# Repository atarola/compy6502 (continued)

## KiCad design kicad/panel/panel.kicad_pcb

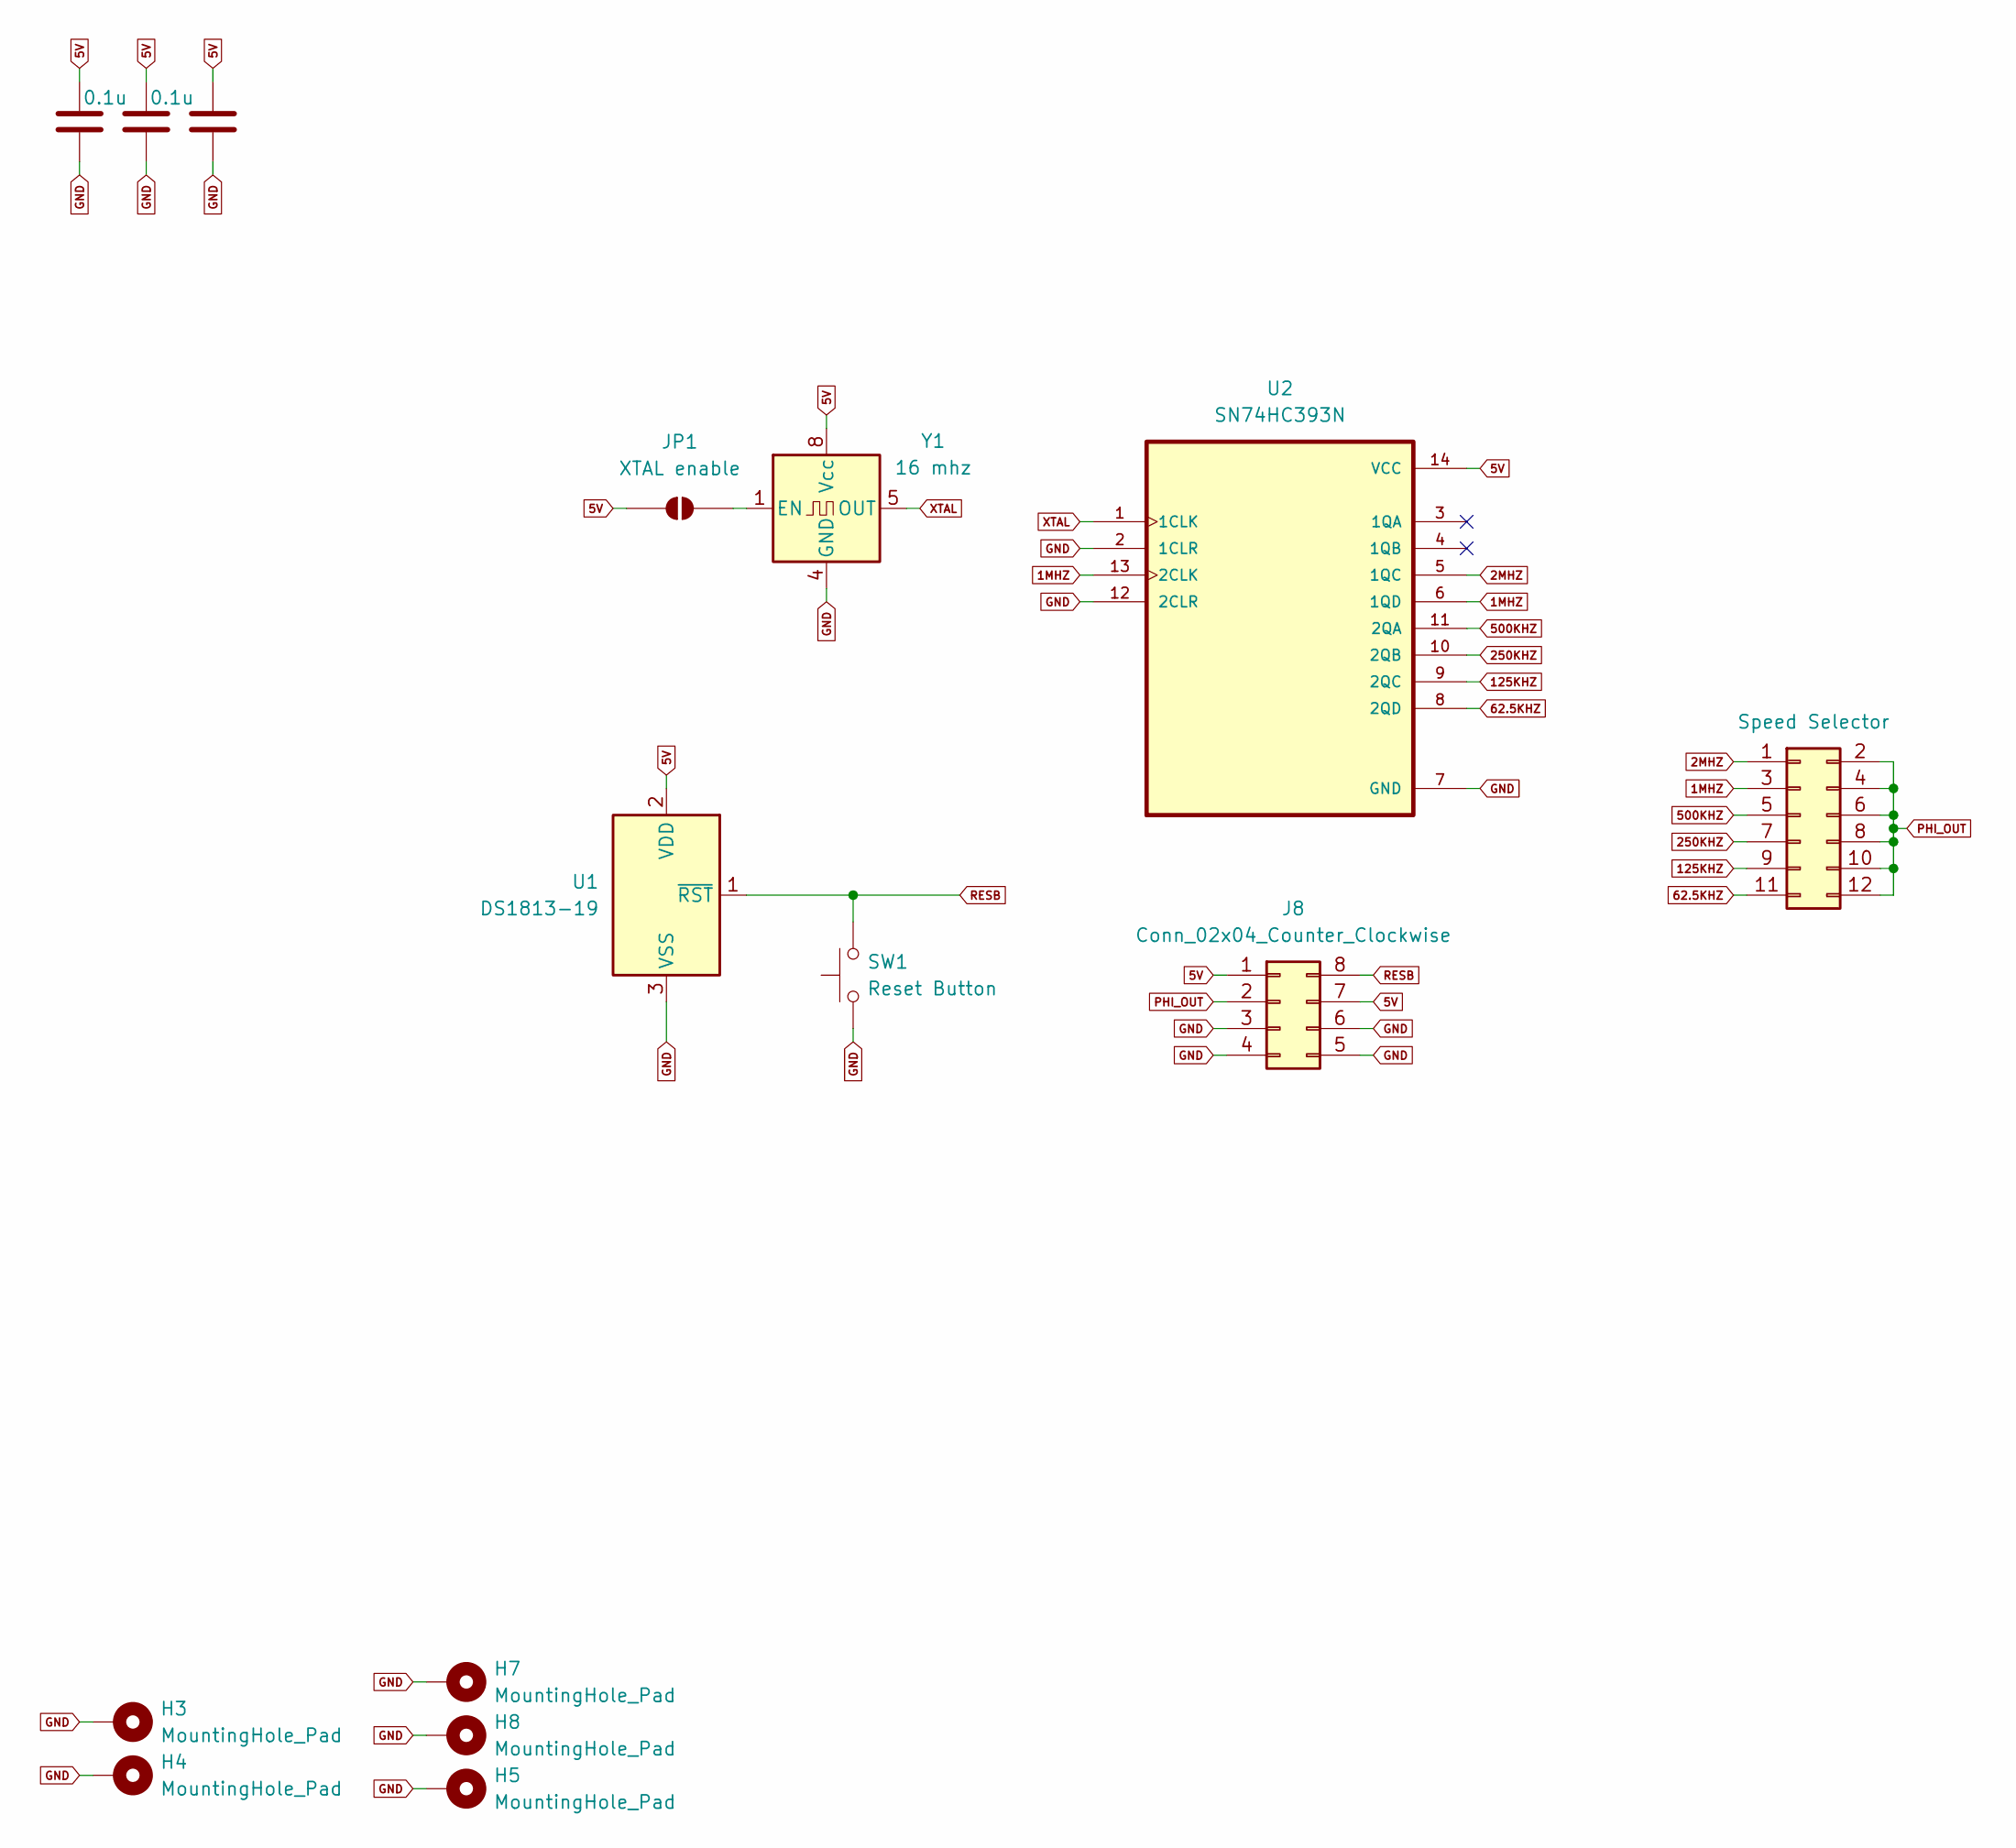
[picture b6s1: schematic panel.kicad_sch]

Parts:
C6, C7, C8: 0.1u; C_Disc_D3.8mm_W2.6mm_P2.50mm
H3, H4, H5, H7, H8: MountingHole_Pad; MountingHole_2.2mm_M2_Pad
J2: Speed Selector; PinHeader_2x06_P2.54mm_Vertical
J8: Conn_02x04_Counter_Clockwise; PinHeader_2x04_P2.54mm_Vertical
JP1: XTAL enable; SolderJumper-2_P1.3mm_Open_TrianglePad1.0x1.5mm
SW1: Reset Button; SW_SPST_Omron_B3F-40xx
U1: DS1813-19; TO-92_Inline
U2: SN74HC393N; DIP-14_W7.62mm_Socket_LongPads
Y1: 16 mhz; Oscillator_DIP-8

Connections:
1MHZ: J2.3, U2.6 (1QD), U2.13 (2CLK)
2MHZ: J2.1, U2.5 (1QC)
5V: C6.1, C7.1, C8.1, J8.1, J8.7, JP1.1 (A), U1.2 (VDD), U2.14 (VCC), Y1.8 (Vcc)
62.5KHZ: J2.11, U2.8 (2QD)
125KHZ: J2.9, U2.9 (2QC)
250KHZ: J2.7, U2.10 (2QB)
500KHZ: J2.5, U2.11 (2QA)
GND: C6.2, C7.2, C8.2, H3.1 (1_1), H4.1 (1_1), H5.1 (1_1), H7.1 (1_1), H8.1 (1_1), J8.3, J8.4, J8.5, J8.6, SW1.1, U1.3 (VSS), U2.2 (1CLR), U2.7 (GND), U2.12 (2CLR), Y1.4 (GND)
unnamed: JP1.2 (B), Y1.1 (EN)
PHI_OUT: J2.2, J2.4, J2.6, J2.8, J2.10, J2.12, J8.2
RESB: J8.8, SW1.2, U1.1 (~RST)
XTAL: U2.1 (1CLK), Y1.5 (OUT)

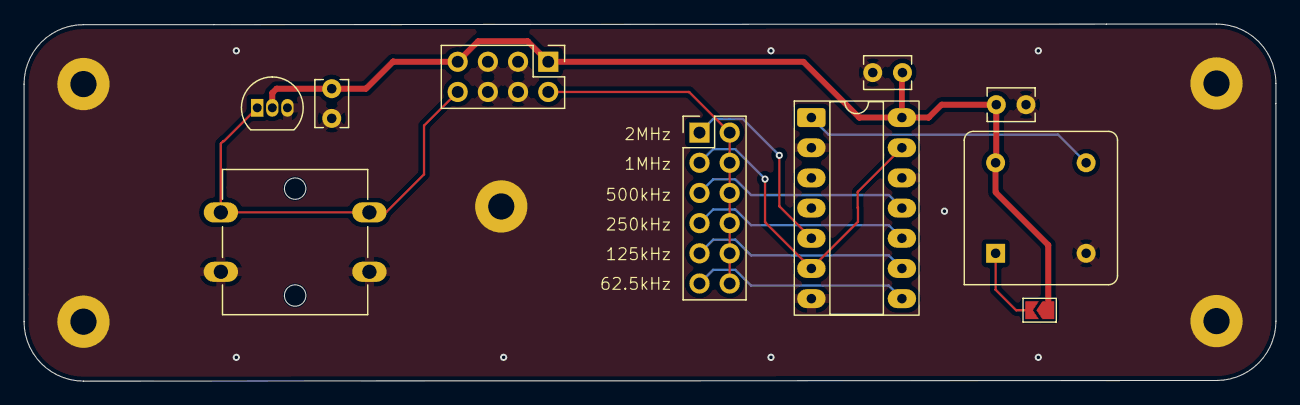
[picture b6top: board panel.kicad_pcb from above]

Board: 2 copper layers, 105.4 x 30.0 mm, 15 parts (0 on the bottom side), 12 nets.

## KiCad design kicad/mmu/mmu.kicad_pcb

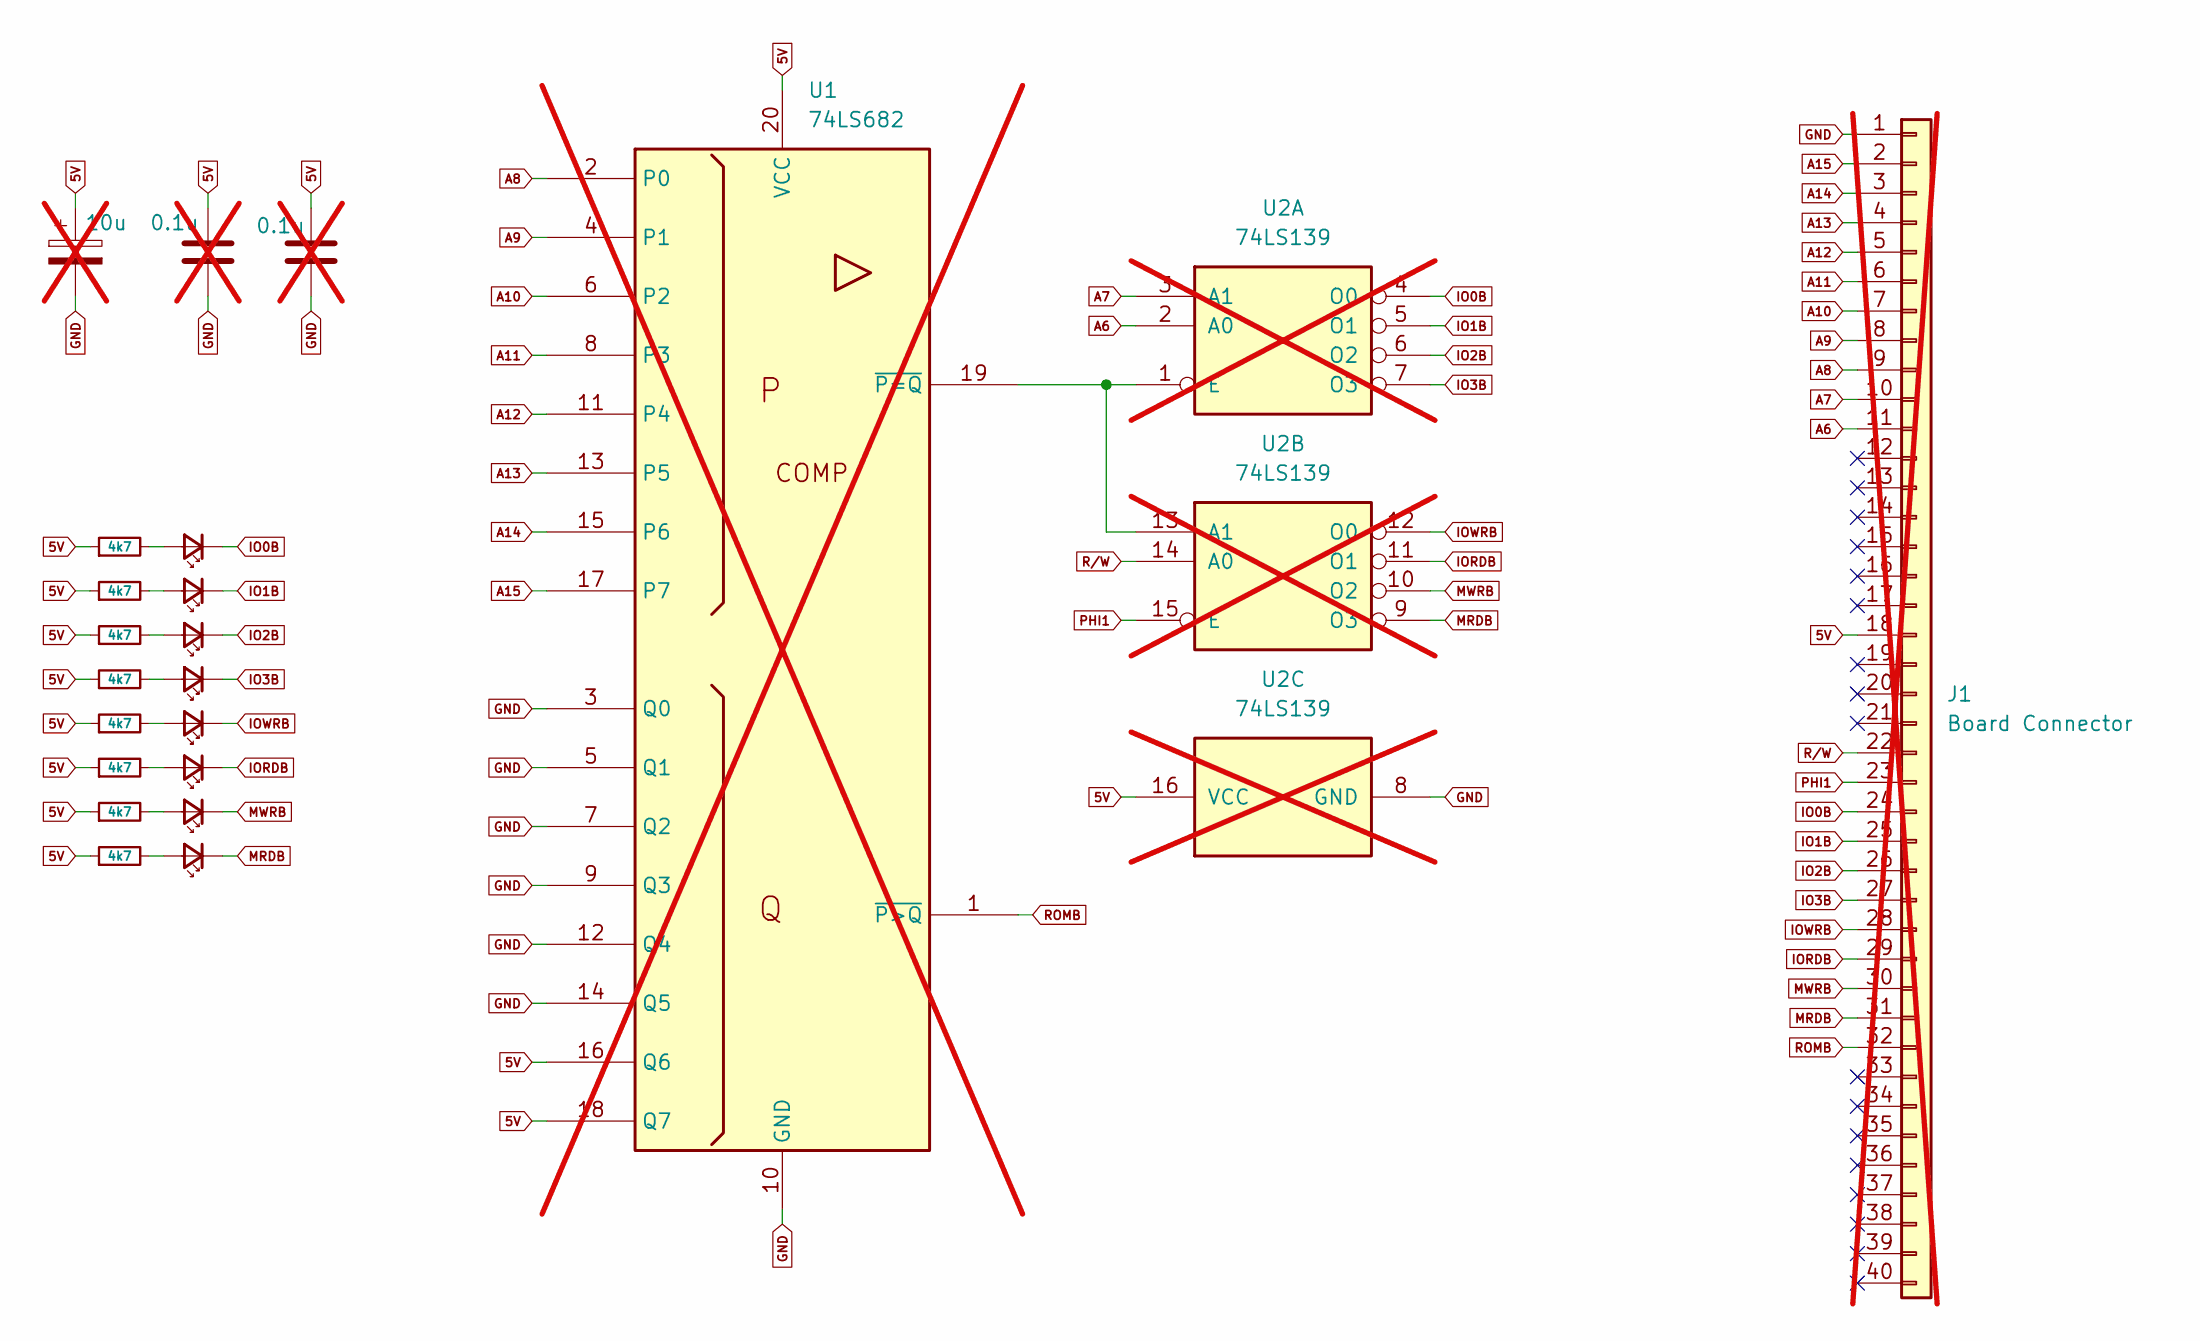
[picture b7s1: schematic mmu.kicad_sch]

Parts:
C1, C2: 0.1u; C_Disc_D3.0mm_W1.6mm_P2.50mm; not fitted
C3: 10u; CP_Radial_D5.0mm_P2.50mm; not fitted
D1, D2, D3, D4, D5, D6, D7, D8: LED_Small; LED_0603_1608Metric
J1: Board Connector; PinHeader_1x40_P2.54mm_Horizontal; not fitted
R1, R2, R3, R4, R5, R6, R7, R8: 4k7; R_0603_1608Metric
U1: 74LS682; DIP-20_W7.62mm_Socket; not fitted
U2: 74LS139; DIP-16_W7.62mm_Socket; not fitted

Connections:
5V: C1.1, C2.1, C3.1, J1.18, R1.1, R2.1, R3.1, R4.1, R5.1, R6.1, R7.1, R8.1, U1.16 (Q6), U1.18 (Q7), U1.20 (VCC), U2.16 (VCC)
A6: J1.11, U2.2 (A0)
A7: J1.10, U2.3 (A1)
A8: J1.9, U1.2 (P0)
A9: J1.8, U1.4 (P1)
A10: J1.7, U1.6 (P2)
A11: J1.6, U1.8 (P3)
A12: J1.5, U1.11 (P4)
A13: J1.4, U1.13 (P5)
A14: J1.3, U1.15 (P6)
A15: J1.2, U1.17 (P7)
GND: C1.2, C2.2, C3.2, J1.1, U1.3 (Q0), U1.5 (Q1), U1.7 (Q2), U1.9 (Q3), U1.10 (GND), U1.12 (Q4), U1.14 (Q5), U2.8 (GND)
IO0B: D1.1 (K), J1.24, U2.4 (O0)
IO1B: D2.1 (K), J1.25, U2.5 (O1)
IO2B: D3.1 (K), J1.26, U2.6 (O2)
IO3B: D4.1 (K), J1.27, U2.7 (O3)
IORDB: D6.1 (K), J1.29, U2.11 (O1)
IOWRB: D5.1 (K), J1.28, U2.12 (O0)
MRDB: D8.1 (K), J1.31, U2.9 (O3)
MWRB: D7.1 (K), J1.30, U2.10 (O2)
unnamed: D1.2 (A), R1.2
unnamed: D2.2 (A), R2.2
unnamed: D3.2 (A), R3.2
unnamed: D4.2 (A), R4.2
unnamed: D5.2 (A), R5.2
unnamed: D6.2 (A), R6.2
unnamed: D7.2 (A), R7.2
unnamed: D8.2 (A), R8.2
unnamed: U1.19 (~P=Q), U2.1 (E), U2.13 (A1)
PHI1: J1.23, U2.15 (E)
ROMB: J1.32, U1.1 (~P>Q)
R/W: J1.22, U2.14 (A0)

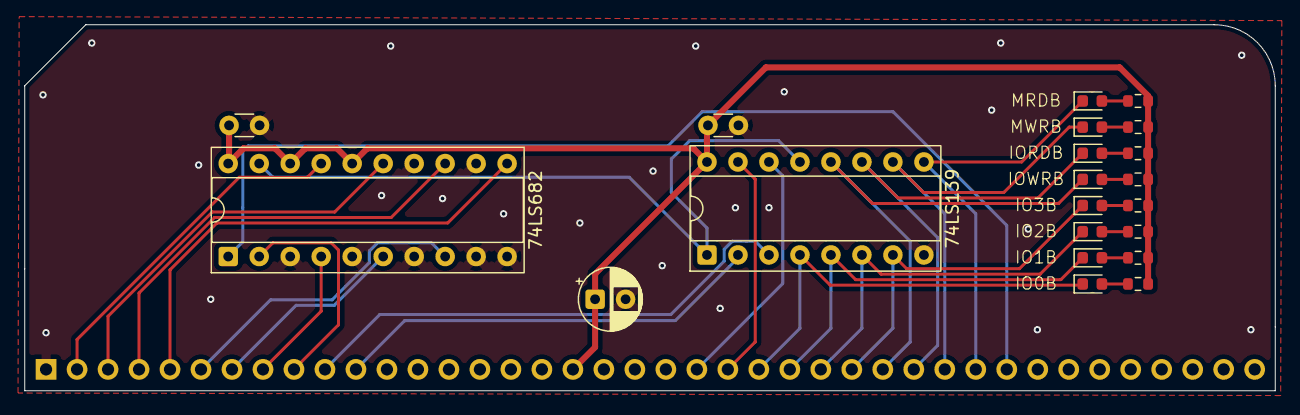
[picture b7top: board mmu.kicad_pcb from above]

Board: 2 copper layers, 102.5 x 30.0 mm, 22 parts (1 on the bottom side), 32 nets.

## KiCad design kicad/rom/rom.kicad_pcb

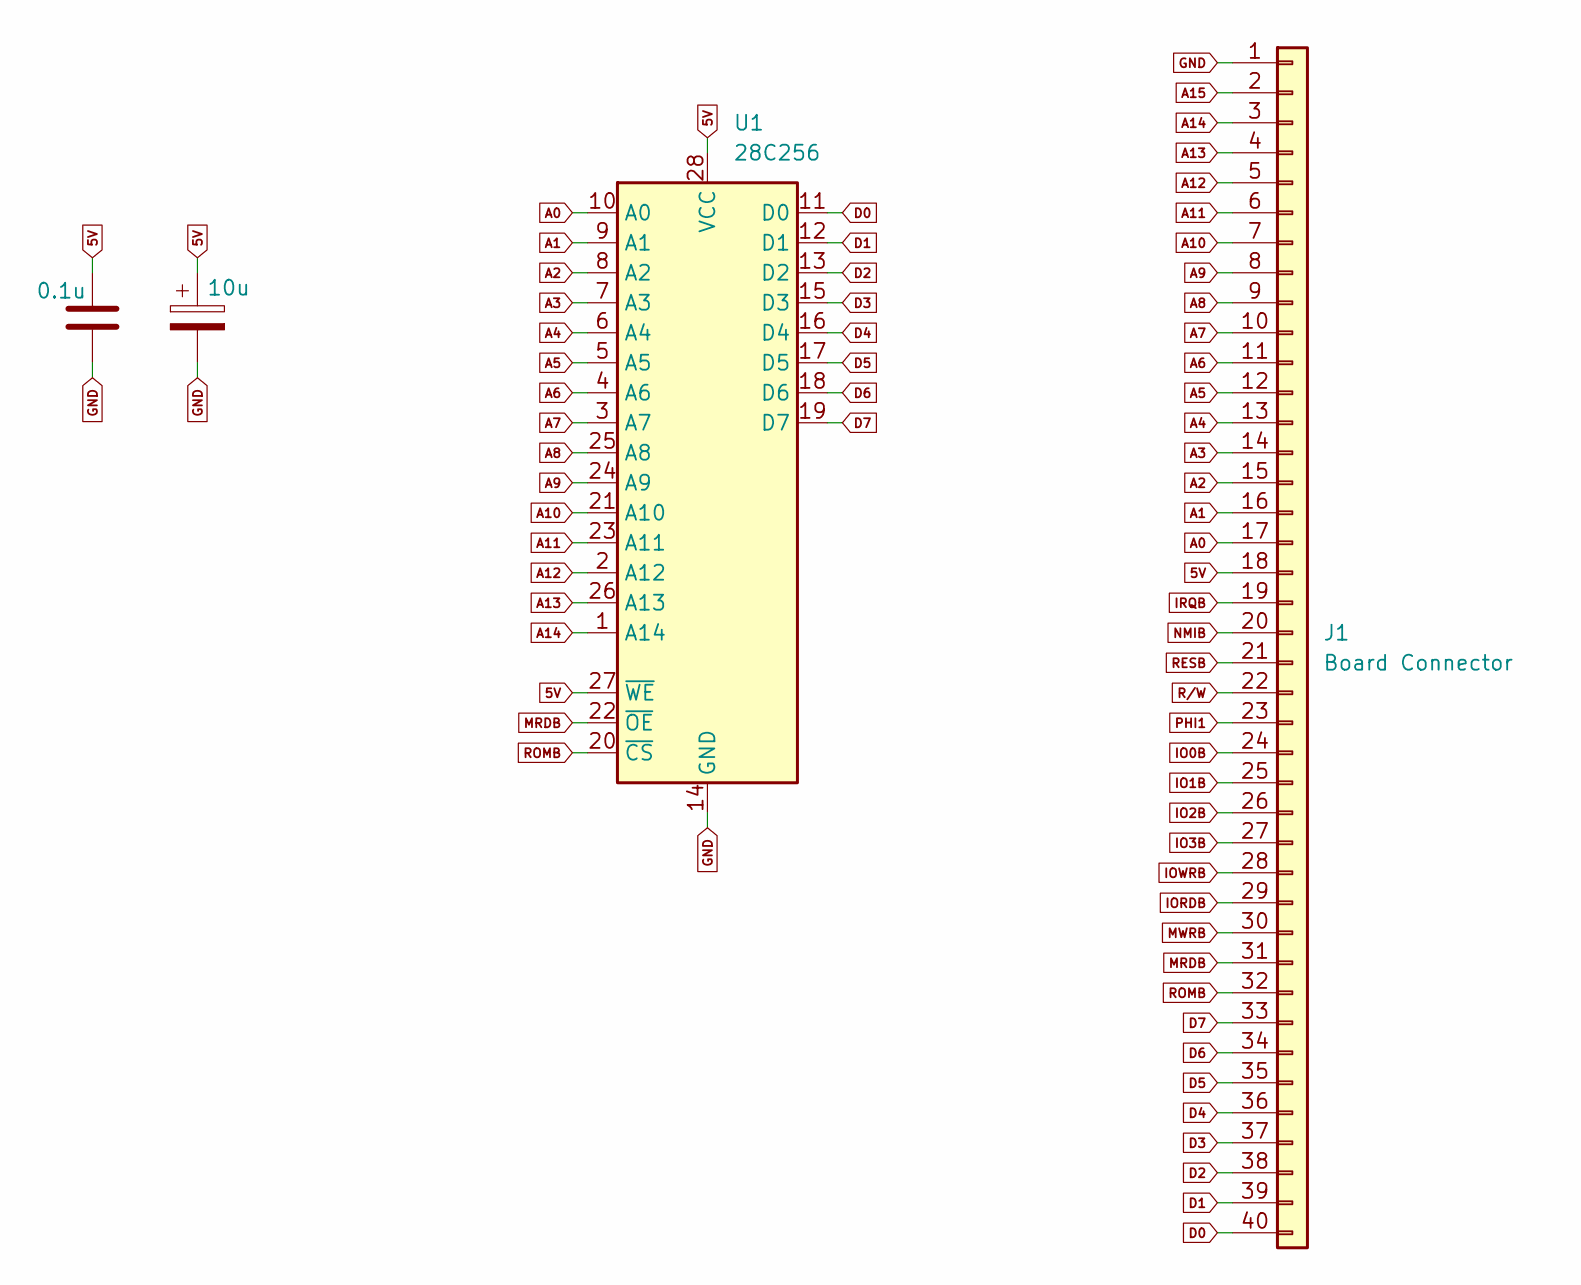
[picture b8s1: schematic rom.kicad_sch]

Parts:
C2: 0.1u; C_Disc_D3.0mm_W1.6mm_P2.50mm
C3: 10u; CP_Radial_D5.0mm_P2.50mm
J1: Board Connector; PinHeader_1x40_P2.54mm_Horizontal
U1: 28C256; DIP_Socket-28_W11.9mm_W12.7mm_W15.24mm_W17.78mm_W18.5mm_3M_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

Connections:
5V: C2.1, C3.1, J1.18, U1.27 (~WE), U1.28 (VCC)
A0: J1.17, U1.10 (A0)
A1: J1.16, U1.9 (A1)
A2: J1.15, U1.8 (A2)
A3: J1.14, U1.7 (A3)
A4: J1.13, U1.6 (A4)
A5: J1.12, U1.5 (A5)
A6: J1.11, U1.4 (A6)
A7: J1.10, U1.3 (A7)
A8: J1.9, U1.25 (A8)
A9: J1.8, U1.24 (A9)
A10: J1.7, U1.21 (A10)
A11: J1.6, U1.23 (A11)
A12: J1.5, U1.2 (A12)
A13: J1.4, U1.26 (A13)
A14: J1.3, U1.1 (A14)
A15: J1.2
D0: J1.40, U1.11 (D0)
D1: J1.39, U1.12 (D1)
D2: J1.38, U1.13 (D2)
D3: J1.37, U1.15 (D3)
D4: J1.36, U1.16 (D4)
D5: J1.35, U1.17 (D5)
D6: J1.34, U1.18 (D6)
D7: J1.33, U1.19 (D7)
GND: C2.2, C3.2, J1.1, U1.14 (GND)
IO0B: J1.24
IO1B: J1.25
IO2B: J1.26
IO3B: J1.27
IORDB: J1.29
IOWRB: J1.28
IRQB: J1.19
MRDB: J1.31, U1.22 (~OE)
MWRB: J1.30
NMIB: J1.20
PHI1: J1.23
RESB: J1.21
ROMB: J1.32, U1.20 (~CS)
R/W: J1.22

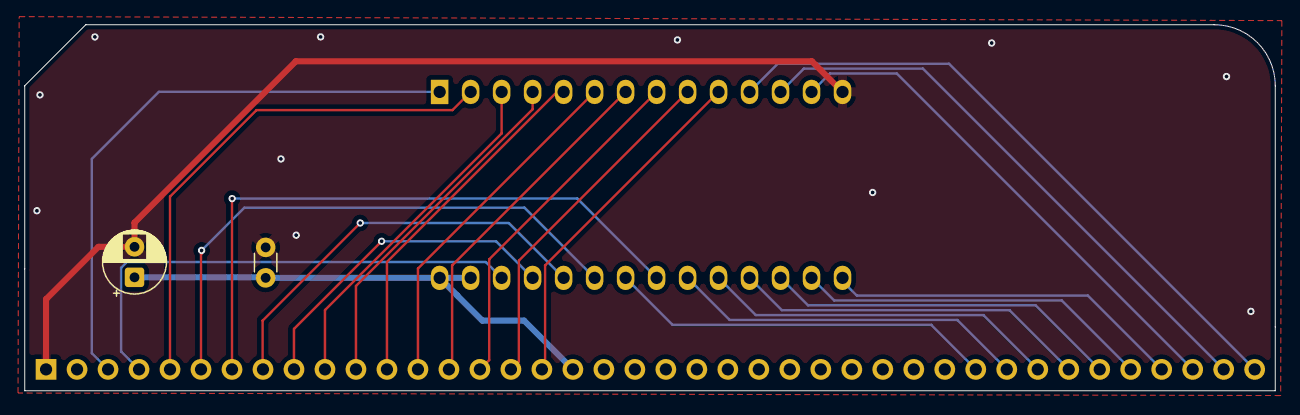
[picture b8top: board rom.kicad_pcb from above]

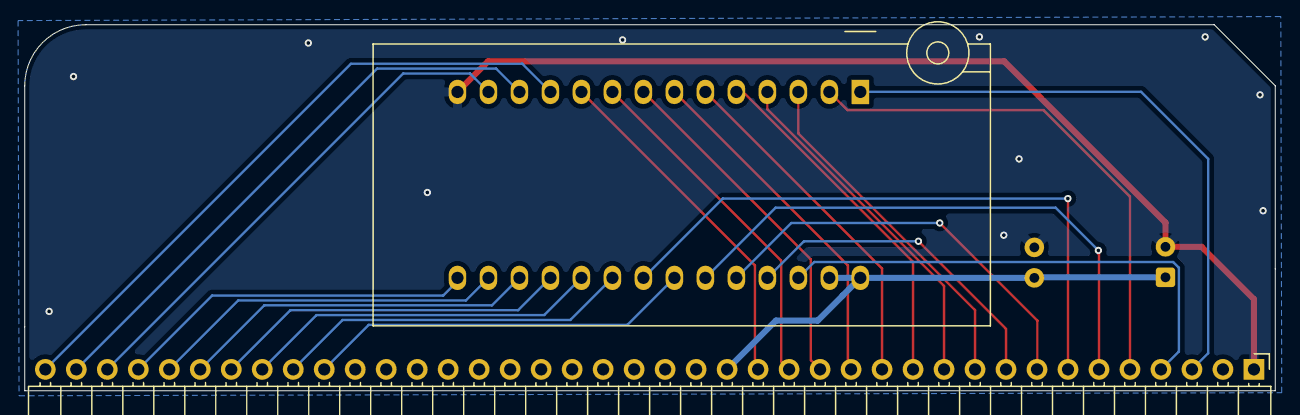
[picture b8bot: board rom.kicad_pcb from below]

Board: 2 copper layers, 102.5 x 30.0 mm, 4 parts (2 on the bottom side), 27 nets.

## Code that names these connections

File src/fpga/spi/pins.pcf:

set_io REG_SELECT[1] A2
set_io REG_SELECT[0] A1

set_io RESB B1
set_io WRB C2
set_io RDB C1

set_io DATA[7] D2
set_io DATA[6] D1
set_io DATA[5] E2
set_io DATA[4] E1
set_io DATA[3] G2
set_io DATA[2] H1
set_io DATA[1] J1
set_io DATA[0] H2

set_io CSB H9

set_io DATA_OUT D9

set_io SPI_CSB[0] D8
set_io SPI_CSB[1] C9
set_io SPI_CSB[2] A9
set_io SPI_CSB[3] B8

set_io SCK A8
set_io MOSI B7
set_io MISO A7

set_io LED B3
set_io USBPU A3
set_io CLK B2

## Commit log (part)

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2019-11-14 finished first pass of acia
2019-11-14 added timer info
2019-11-18 checkpoint
2019-11-21 back to basics
2019-11-22 blinkenlights
2019-11-22 acia working!
2019-11-24 ram test
2019-11-24 finished sstore and sfetch
2019-11-24 finished basic stack
2019-11-24 renamed properly
2019-11-26 unit tested most of the stack subroutines
2019-11-26 started to test the acia
2019-11-27 finished acia tests
2021-12-27 removed acia, added spi
2026-05-02 reboot project
2026-05-02 cleaned up info
2026-05-02 moved the python stuff to modern frameworks
2026-05-03 updated notes
2026-05-03 removed inprogress notes
2026-05-03 start on wozmon
2026-05-04 integrated wozmon, updated kicad to specify phi1o
2026-05-04 added acia board
2026-05-04 mark the ACIA card as complete
2026-05-05 designed the front panel
2026-05-05 remove errant lock files
2026-05-05 started ROM ABI setup
2026-05-07 make room for verilog
2026-05-07 added doit as a task runner
2026-05-07 setup a verilog workflow
2026-05-07 run programmer in windows, usb over wsl2 is obnoxious
2026-05-07 updated fpga framework to handle multiple modules
2026-05-09 got the beginnings of the engine setup, and the first test
2026-05-09 fixed timing issue with register shift signals
2026-05-09 working through timings of back to back signals
2026-05-09 removed done state, since its just the inverse of busy
2026-05-09 added a busy signal
2026-05-09 removed spi chip select from the engine
2026-05-09 added stub tests for the controller
2026-05-09 make sure all .v files have default_nettype none
2026-05-10 split the bus into input and outputs in the controller
2026-05-10 finished controller tests
2026-05-10 setup final shape, force cs updates per config register
2026-05-10 cleanup and readme generation
2026-05-10 fpga readme tweaks
2026-05-10 added select flags to readme
2026-05-10 drive a pin for handling level shifting
2026-05-10 added board numbers to pin descriptions
2026-05-11 added arduino test harness
2026-05-14 version 1 of the SPI board
2026-05-15 setup eventual console output
2026-05-15 moved stuff around, built srect generator
2026-05-15 finished up the uploading tooling from the computer side
2026-05-16 added s-record loader script to wozmon
2026-05-16 started off on some programs
2026-05-17 started on a forth
2026-05-17 defined basic forth words to implement
2026-05-17 changed name and custom word storage to a heap
2026-05-18 finished the forth primatives
2026-05-18 checkpoint: added beginnings of compilation
2026-05-18 added first pass of the compiler
2026-05-18 finished compiler
2026-05-21 added spi and via boards
2026-05-21 added rot as a base word
2026-05-21 added backspace to forth shell
2026-05-22 updated fpga to have selectable speeds
2026-05-23 setup IRQ stuff
2026-05-23 added helpers for string editing
2026-05-24 add str_eq, make sure the code compiles
2026-05-24 add new sting subprocedures to the jumptable
2026-05-24 added ansi control characters, fixed srec tests
2026-05-24 Revert "added ansi control characters, fixed srec tests"
    This reverts commit 78bdfd051a490e4e383977094991fc1daca26eb9.
2026-05-24 fix srec loader tests
2026-05-24 setup more testing around the rom subprocedures
2026-05-24 moved test files to new names, added line editor
2026-05-25 extracted the line editor to a rom subroutine
2026-05-25 added some comments to jog my memory
2026-05-25 made forth a first-class citizen
2026-05-25 last minute cleanup of forth move
2026-05-25 added more string handling functions
2026-05-25 prepping for control flow
2026-05-25 loop and until
2026-05-26 allow 16bit immediates
2026-05-26 if else endif
2026-05-26 added repeat and while
2026-05-26 comparison stubs
2026-05-26 moved to 256 words from 128
2026-05-26 comparison operators
2026-05-28 got the spi controller controlling
2026-05-29 setup the fram properly
2026-05-29 finished up the fram driver
2026-05-31 cleanup some code
2026-05-31 switiching from windows storage to git
2026-05-31 some doc cleanup
2026-05-31 added tests for SPI and FRAM
2026-06-04 got the console writing from the keyboard
2026-06-05 worlds worst word processor
2026-06-05 wrong spi host
2026-06-06 finished the console
2026-06-06 finished console mode
2026-06-06 starting on rust port of console
2026-06-06 stubbed out interactions between modules
2026-06-06 stubbed stuff out, started on the display.rs
2026-06-06 display_task doesnt need the pd pin
2026-06-07 screen is booting... again
2026-06-07 ported over ansi text handling
2026-06-07 finished porting the text pipeline to rust
2026-06-07 stress testing the queue
2026-06-11 got display working, starting on keyboard
2026-06-11 dinking around with the stubs
2026-06-12 ported some code to rust, for the memes
2026-06-13 finished keyboard wiring
2026-06-16 tracked down the spi FF bug
2026-06-16 started on math routines
2026-06-17 added fs_write, cleaned up superblock
2026-06-19 moved the 16bit math to macros, did fs_find
2026-06-19 fixed some bugs with the find
2026-06-19 remove the arduino code
2026-06-20 added fs_delete, sped up srec uploading
2026-06-20 implemented write and update
2026-06-20 fs_compact done
2026-06-20 split fs.s up, reorg
2026-06-20 fixed forth error
